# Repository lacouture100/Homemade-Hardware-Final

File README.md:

# Homemade-Hardware-Final
Repository for the development of my Homemade Hardware project.

Link to documentation: https://www.notion.so/alvarolacouture/Final-Project-Presentation-92cd7def9d2d4c558a401a928ef00175

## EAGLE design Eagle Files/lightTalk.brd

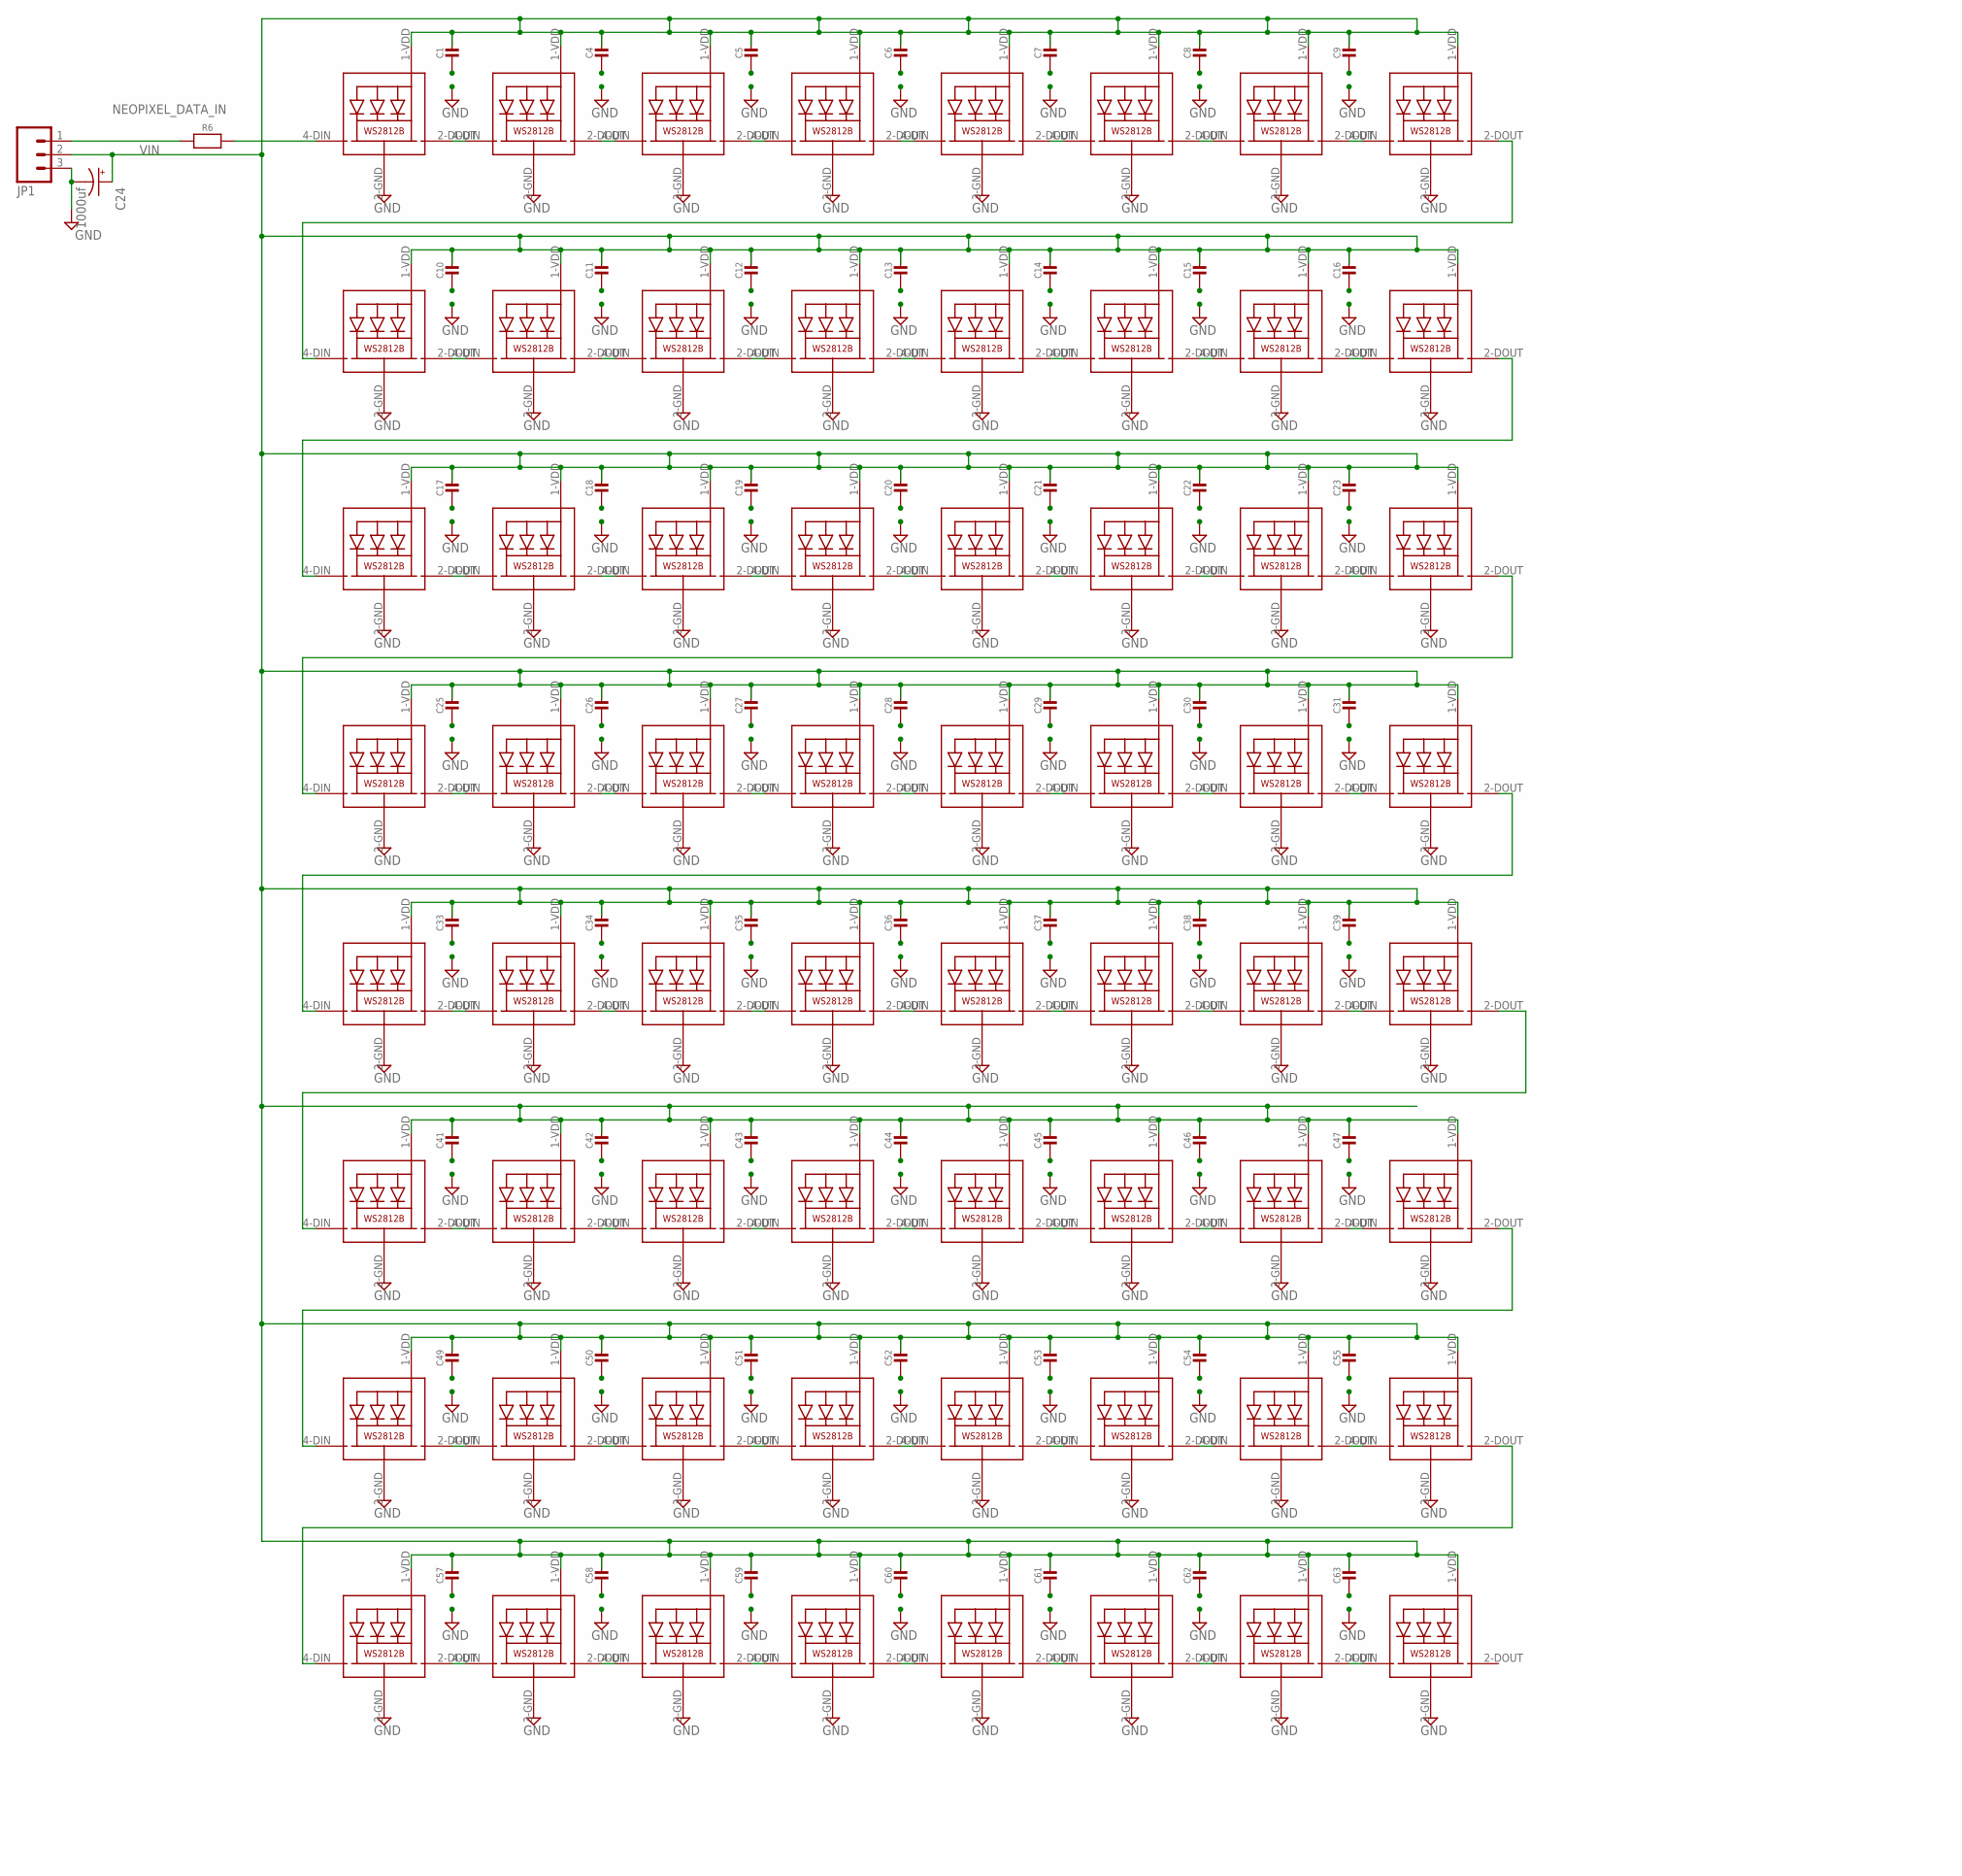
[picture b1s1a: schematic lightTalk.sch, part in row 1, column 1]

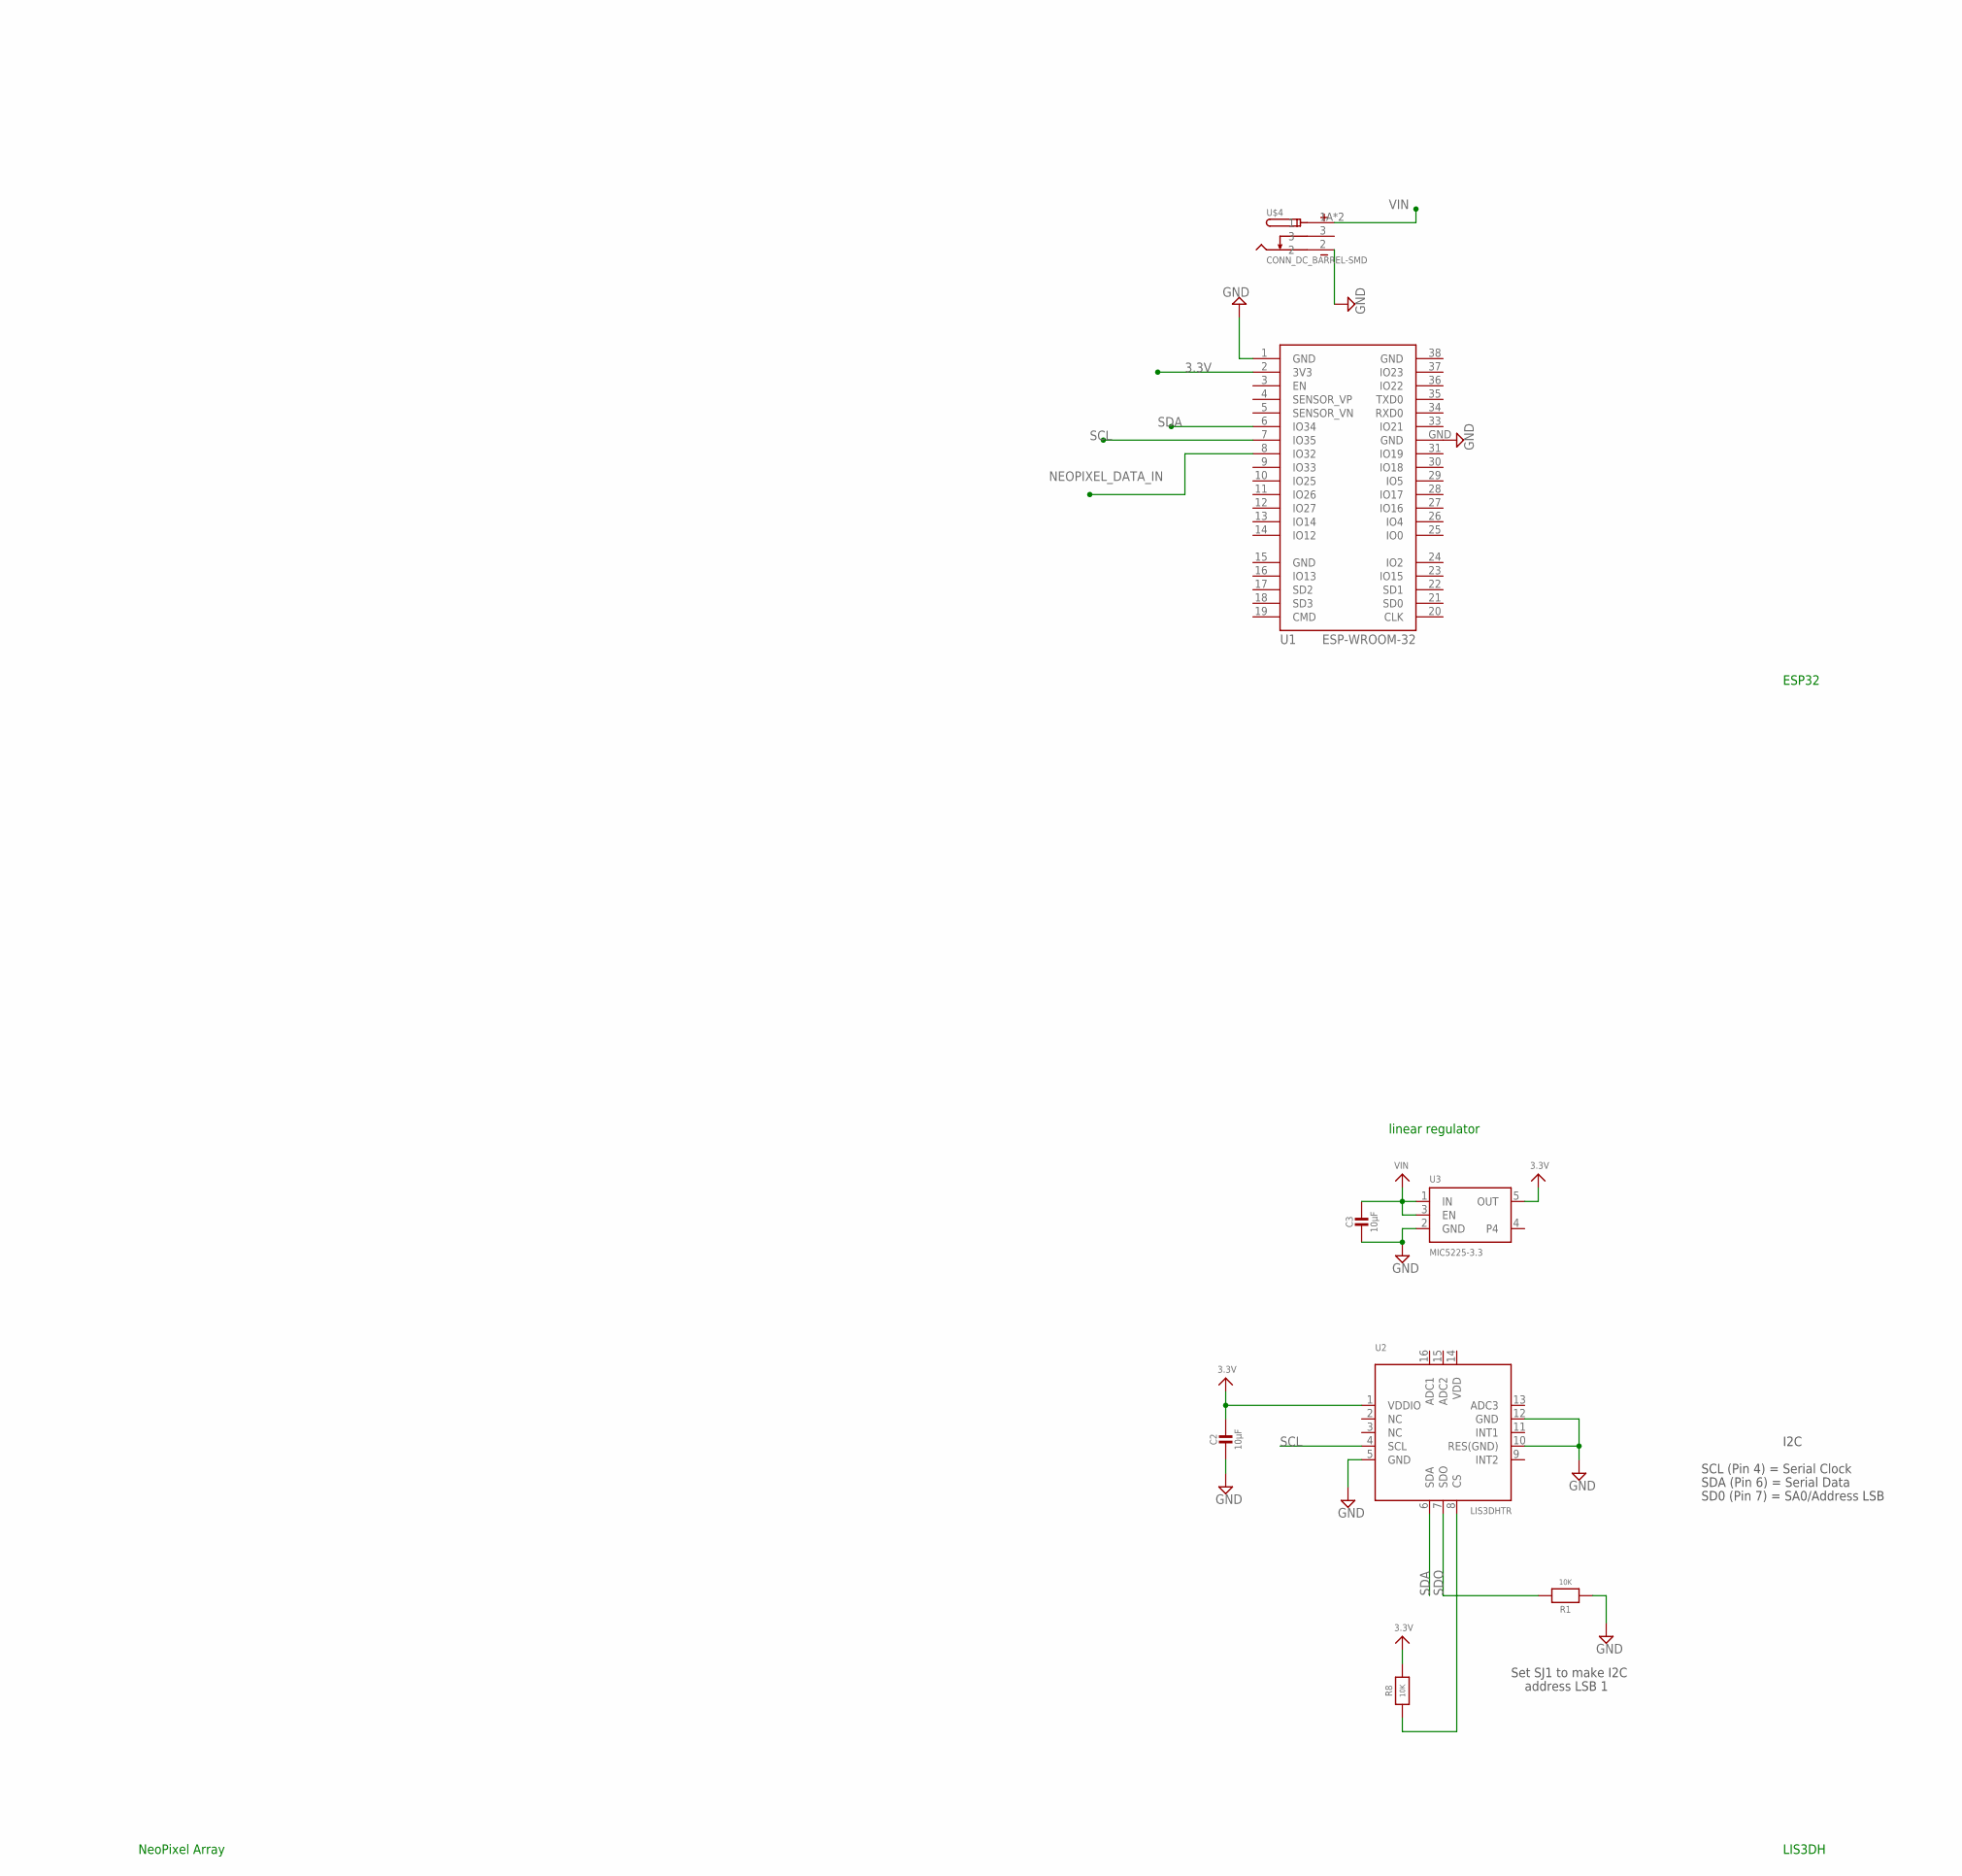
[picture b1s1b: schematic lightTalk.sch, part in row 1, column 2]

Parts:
C1, C4, C5, C6, C7, C8, C9, C10, C11, C12, C13, C14, C15, C16, C17, C18, C19, C20, C21, C22, C23, C25, C26, C27, C28, C29, C30, C31, C33, C34, C35, C36, C37, C38, C39, C41, C42, C43, C44, C45, C46, C47, C49, C50, C51, C52, C53, C54, C55, C57, C58, C59, C60, C61, C62, C63: CAP_CERAMIC0805-NOOUTLINE; 0805-NO
C2, C3: 10µF; 0805-NO
C24: 1000uf; CAP_RADIAL_CAN_10MM
JP1: M03PTH; 1X03
LED1, LED2, LED3, LED4, LED5, LED6, LED7, LED8, LED9, LED10, LED11, LED12, LED13, LED14, LED15, LED16, LED17, LED18, LED19, LED20, LED21, LED22, LED23, LED24, LED25, LED26, LED27, LED28, LED29, LED30, LED31, LED32, LED33, LED34, LED35, LED36, LED37, LED38, LED39, LED40, LED41, LED42, LED43, LED44, LED45, LED46, LED47, LED48, LED49, LED50, LED51, LED52, LED53, LED54, LED55, LED56, LED57, LED58, LED59, LED60, LED61, LED62, LED63, LED64: WS2812B5050; WS2812B
R1, R8: 10K; 0805-NO
R6: RESISTOR0805_NOOUTLINE; 0805-NO
U1: ESP-WROOM-32
U2: LIS3DHTR; LGA16_3X3MM
U3: MIC5225-3.3; SOT23-5
U$4: CONN_DC_BARREL-SMD; 694106106102

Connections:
3.3V: C2.1, R8.2, U1.2 (3V3), U2.1 (VDDIO), U3.5 (OUT)
GND: C1.2, C2.2, C3.2, C4.2, C5.2, C6.2, C7.2, C8.2, C9.2, C10.2, C11.2, C12.2, C13.2, C14.2, C15.2, C16.2, C17.2, C18.2, C19.2, C20.2, C21.2, C22.2, C23.2, C24.-, C25.2, C26.2, C27.2, C28.2, C29.2, C30.2, C31.2, C33.2, C34.2, C35.2, C36.2, C37.2, C38.2, C39.2, C41.2, C42.2, C43.2, C44.2, C45.2, C46.2, C47.2, C49.2, C50.2, C51.2, C52.2, C53.2, C54.2, C55.2, C57.2, C58.2, C59.2, C60.2, C61.2, C62.2, C63.2, JP1.3, LED1.3-GND (GND), LED2.3-GND (GND), LED3.3-GND (GND), LED4.3-GND (GND), LED5.3-GND (GND), LED6.3-GND (GND), LED7.3-GND (GND), LED8.3-GND (GND), LED9.3-GND (GND), LED10.3-GND (GND), LED11.3-GND (GND), LED12.3-GND (GND), LED13.3-GND (GND), LED14.3-GND (GND), LED15.3-GND (GND), LED16.3-GND (GND), LED17.3-GND (GND), LED18.3-GND (GND), LED19.3-GND (GND), LED20.3-GND (GND), LED21.3-GND (GND), LED22.3-GND (GND), LED23.3-GND (GND), LED24.3-GND (GND), LED25.3-GND (GND), LED26.3-GND (GND), LED27.3-GND (GND), LED28.3-GND (GND), LED29.3-GND (GND), LED30.3-GND (GND), LED31.3-GND (GND), LED32.3-GND (GND), LED33.3-GND (GND), LED34.3-GND (GND), LED35.3-GND (GND), LED36.3-GND (GND), LED37.3-GND (GND), LED38.3-GND (GND), LED39.3-GND (GND), LED40.3-GND (GND), LED41.3-GND (GND), LED42.3-GND (GND), LED43.3-GND (GND), LED44.3-GND (GND), LED45.3-GND (GND), LED46.3-GND (GND), LED47.3-GND (GND), LED48.3-GND (GND), LED49.3-GND (GND), LED50.3-GND (GND), LED51.3-GND (GND), LED52.3-GND (GND), LED53.3-GND (GND), LED54.3-GND (GND), LED55.3-GND (GND), LED56.3-GND (GND), LED57.3-GND (GND), LED58.3-GND (GND), LED59.3-GND (GND), LED60.3-GND (GND), LED61.3-GND (GND), LED62.3-GND (GND), LED63.3-GND (GND), LED64.3-GND (GND), R1.1, U1.1 (GND), U1.15 (GND), U1.38 (GND), U1.GND, U2.5 (GND), U2.10 (RES(GND)), U2.12 (GND), U3.2 (GND), U$4.2
unnamed: LED8.2-DOUT (DO), LED9.4-DIN (DI)
unnamed: R8.1, U2.8 (CS)
unnamed: LED16.2-DOUT (DO), LED17.4-DIN (DI)
unnamed: LED24.2-DOUT (DO), LED25.4-DIN (DI)
unnamed: LED40.2-DOUT (DO), LED41.4-DIN (DI)
unnamed: LED32.2-DOUT (DO), LED33.4-DIN (DI)
unnamed: LED48.2-DOUT (DO), LED49.4-DIN (DI)
unnamed: LED56.2-DOUT (DO), LED57.4-DIN (DI)
unnamed: LED1.4-DIN (DI), R6.2
unnamed: LED17.2-DOUT (DO), LED18.4-DIN (DI)
unnamed: LED25.2-DOUT (DO), LED26.4-DIN (DI)
unnamed: LED26.2-DOUT (DO), LED27.4-DIN (DI)
unnamed: LED2.2-DOUT (DO), LED3.4-DIN (DI)
unnamed: LED3.2-DOUT (DO), LED4.4-DIN (DI)
unnamed: LED4.2-DOUT (DO), LED5.4-DIN (DI)
unnamed: LED5.2-DOUT (DO), LED6.4-DIN (DI)
unnamed: LED6.2-DOUT (DO), LED7.4-DIN (DI)
unnamed: LED7.2-DOUT (DO), LED8.4-DIN (DI)
unnamed: LED10.2-DOUT (DO), LED11.4-DIN (DI)
unnamed: LED11.2-DOUT (DO), LED12.4-DIN (DI)
unnamed: LED12.2-DOUT (DO), LED13.4-DIN (DI)
unnamed: LED13.2-DOUT (DO), LED14.4-DIN (DI)
unnamed: LED14.2-DOUT (DO), LED15.4-DIN (DI)
unnamed: LED15.2-DOUT (DO), LED16.4-DIN (DI)
unnamed: LED18.2-DOUT (DO), LED19.4-DIN (DI)
unnamed: LED19.2-DOUT (DO), LED20.4-DIN (DI)
unnamed: LED20.2-DOUT (DO), LED21.4-DIN (DI)
unnamed: LED21.2-DOUT (DO), LED22.4-DIN (DI)
unnamed: LED22.2-DOUT (DO), LED23.4-DIN (DI)
unnamed: LED23.2-DOUT (DO), LED24.4-DIN (DI)
unnamed: LED27.2-DOUT (DO), LED28.4-DIN (DI)
unnamed: LED28.2-DOUT (DO), LED29.4-DIN (DI)
unnamed: LED29.2-DOUT (DO), LED30.4-DIN (DI)
unnamed: LED30.2-DOUT (DO), LED31.4-DIN (DI)
unnamed: LED31.2-DOUT (DO), LED32.4-DIN (DI)
unnamed: LED1.2-DOUT (DO), LED2.4-DIN (DI)
unnamed: LED9.2-DOUT (DO), LED10.4-DIN (DI)
unnamed: LED49.2-DOUT (DO), LED50.4-DIN (DI)
unnamed: LED57.2-DOUT (DO), LED58.4-DIN (DI)
unnamed: LED58.2-DOUT (DO), LED59.4-DIN (DI)
unnamed: LED34.2-DOUT (DO), LED35.4-DIN (DI)
unnamed: LED35.2-DOUT (DO), LED36.4-DIN (DI)
unnamed: LED36.2-DOUT (DO), LED37.4-DIN (DI)
unnamed: LED37.2-DOUT (DO), LED38.4-DIN (DI)
unnamed: LED38.2-DOUT (DO), LED39.4-DIN (DI)
unnamed: LED39.2-DOUT (DO), LED40.4-DIN (DI)
unnamed: LED42.2-DOUT (DO), LED43.4-DIN (DI)
unnamed: LED43.2-DOUT (DO), LED44.4-DIN (DI)
unnamed: LED44.2-DOUT (DO), LED45.4-DIN (DI)
unnamed: LED45.2-DOUT (DO), LED46.4-DIN (DI)
unnamed: LED46.2-DOUT (DO), LED47.4-DIN (DI)
unnamed: LED47.2-DOUT (DO), LED48.4-DIN (DI)
unnamed: LED50.2-DOUT (DO), LED51.4-DIN (DI)
unnamed: LED51.2-DOUT (DO), LED52.4-DIN (DI)
unnamed: LED52.2-DOUT (DO), LED53.4-DIN (DI)
unnamed: LED53.2-DOUT (DO), LED54.4-DIN (DI)
unnamed: LED54.2-DOUT (DO), LED55.4-DIN (DI)
unnamed: LED55.2-DOUT (DO), LED56.4-DIN (DI)
unnamed: LED59.2-DOUT (DO), LED60.4-DIN (DI)
unnamed: LED60.2-DOUT (DO), LED61.4-DIN (DI)
unnamed: LED61.2-DOUT (DO), LED62.4-DIN (DI)
unnamed: LED62.2-DOUT (DO), LED63.4-DIN (DI)
unnamed: LED63.2-DOUT (DO), LED64.4-DIN (DI)
unnamed: LED33.2-DOUT (DO), LED34.4-DIN (DI)
unnamed: LED41.2-DOUT (DO), LED42.4-DIN (DI)
NEOPIXEL_DATA_IN: JP1.1, R6.1, U1.8 (IO32)
SCL: U1.7 (IO35), U2.4 (SCL)
SDA: U1.6 (IO34), U2.6 (SDA)
SDO: R1.2, U2.7 (SDO)
VIN: C1.1, C3.1, C4.1, C5.1, C6.1, C7.1, C8.1, C9.1, C10.1, C11.1, C12.1, C13.1, C14.1, C15.1, C16.1, C17.1, C18.1, C19.1, C20.1, C21.1, C22.1, C23.1, C24.+, C25.1, C26.1, C27.1, C28.1, C29.1, C30.1, C31.1, C33.1, C34.1, C35.1, C36.1, C37.1, C38.1, C39.1, C41.1, C42.1, C43.1, C44.1, C45.1, C46.1, C47.1, C49.1, C50.1, C51.1, C52.1, C53.1, C54.1, C55.1, C57.1, C58.1, C59.1, C60.1, C61.1, C62.1, C63.1, JP1.2, LED1.1-VDD (VDD), LED2.1-VDD (VDD), LED3.1-VDD (VDD), LED4.1-VDD (VDD), LED5.1-VDD (VDD), LED6.1-VDD (VDD), LED7.1-VDD (VDD), LED8.1-VDD (VDD), LED9.1-VDD (VDD), LED10.1-VDD (VDD), LED11.1-VDD (VDD), LED12.1-VDD (VDD), LED13.1-VDD (VDD), LED14.1-VDD (VDD), LED15.1-VDD (VDD), LED16.1-VDD (VDD), LED17.1-VDD (VDD), LED18.1-VDD (VDD), LED19.1-VDD (VDD), LED20.1-VDD (VDD), LED21.1-VDD (VDD), LED22.1-VDD (VDD), LED23.1-VDD (VDD), LED24.1-VDD (VDD), LED25.1-VDD (VDD), LED26.1-VDD (VDD), LED27.1-VDD (VDD), LED28.1-VDD (VDD), LED29.1-VDD (VDD), LED30.1-VDD (VDD), LED31.1-VDD (VDD), LED32.1-VDD (VDD), LED33.1-VDD (VDD), LED34.1-VDD (VDD), LED35.1-VDD (VDD), LED36.1-VDD (VDD), LED37.1-VDD (VDD), LED38.1-VDD (VDD), LED39.1-VDD (VDD), LED40.1-VDD (VDD), LED41.1-VDD (VDD), LED42.1-VDD (VDD), LED43.1-VDD (VDD), LED44.1-VDD (VDD), LED45.1-VDD (VDD), LED46.1-VDD (VDD), LED47.1-VDD (VDD), LED48.1-VDD (VDD), LED49.1-VDD (VDD), LED50.1-VDD (VDD), LED51.1-VDD (VDD), LED52.1-VDD (VDD), LED53.1-VDD (VDD), LED54.1-VDD (VDD), LED55.1-VDD (VDD), LED56.1-VDD (VDD), LED57.1-VDD (VDD), LED58.1-VDD (VDD), LED59.1-VDD (VDD), LED60.1-VDD (VDD), LED61.1-VDD (VDD), LED62.1-VDD (VDD), LED63.1-VDD (VDD), LED64.1-VDD (VDD), U3.1 (IN), U3.3 (EN), U$4.1A (1), U$4.1B (1)

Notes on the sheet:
I2C
SCL (Pin 4) = Serial Clock
SDA (Pin 6) = Serial Data
SD0 (Pin 7) = SA0/Address LSB
Set SJ1 to make I2C
address LSB 1
linear regulator
NeoPixel Array
LIS3DH
ESP32

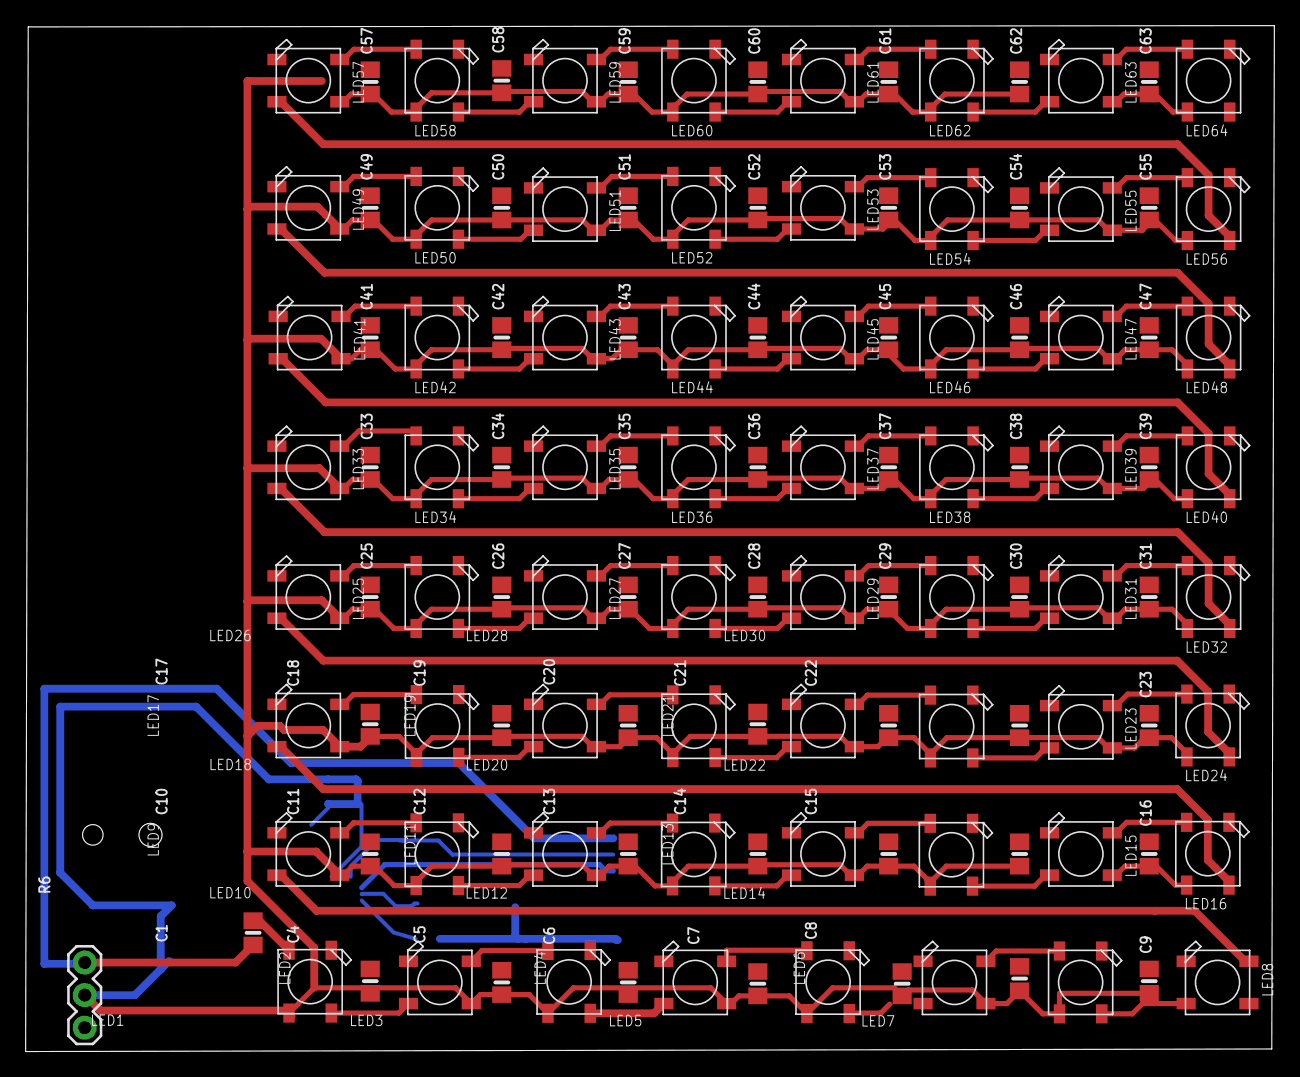
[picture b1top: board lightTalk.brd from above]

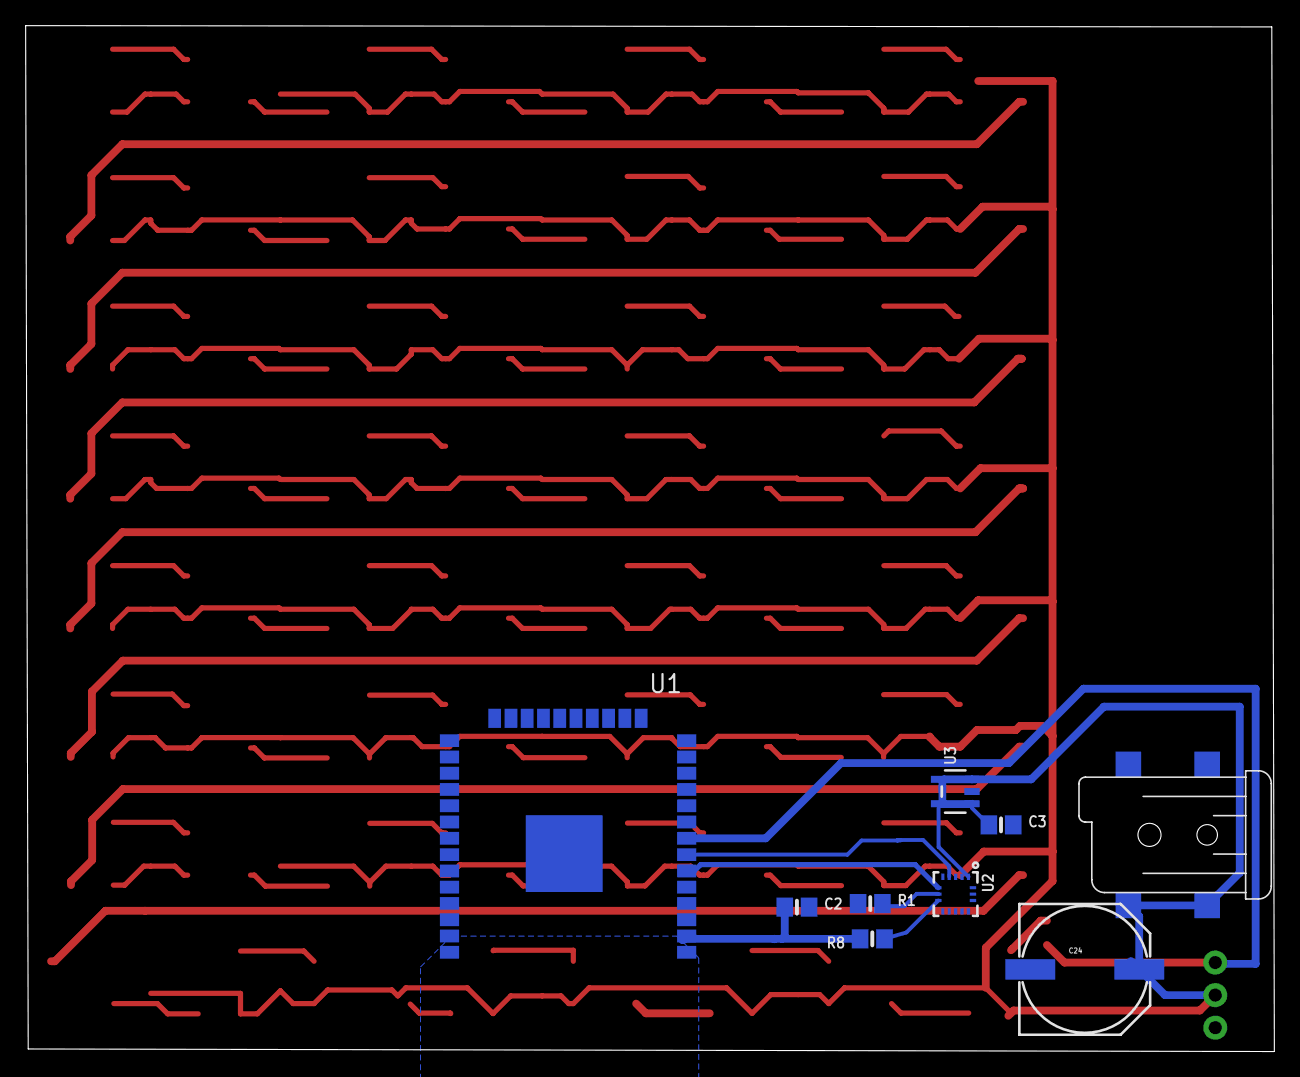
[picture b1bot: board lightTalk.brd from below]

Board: 2 copper layers, 97.4 x 80.0 mm, 131 parts (9 on the bottom side), 72 nets.

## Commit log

2020-04-03 Added arduino sketches
2020-04-24 Updated with working Websockets Server and clients
2020-05-19 Updated Notion Link
2020-12-12 Bump ini from 1.3.5 to 1.3.8 in /NodeJS/WSServer
    Bumps [ini](https://github.com/isaacs/ini) from 1.3.5 to 1.3.8.
    - [Release notes](https://github.com/isaacs/ini/releases)
    - [Commits](https://github.com/isaacs/ini/compare/v1.3.5...v1.3.8)
2021-06-11 Bump normalize-url from 4.5.0 to 4.5.1 in /NodeJS/WSServer
    Bumps [normalize-url](https://github.com/sindresorhus/normalize-url) from 4.5.0 to 4.5.1.
    - [Release notes](https://github.com/sindresorhus/normalize-url/releases)
    - [Commits](https://github.com/sindresorhus/normalize-url/commits)
    ---
    updated-dependencies:
    - dependency-name: normalize-url
2021-06-11 Bump glob-parent from 5.1.1 to 5.1.2 in /NodeJS/WSServer
    Bumps [glob-parent](https://github.com/gulpjs/glob-parent) from 5.1.1 to 5.1.2.
    - [Release notes](https://github.com/gulpjs/glob-parent/releases)
    - [Changelog](https://github.com/gulpjs/glob-parent/blob/main/CHANGELOG.md)
    - [Commits](https://github.com/gulpjs/glob-parent/compare/v5.1.1...v5.1.2)
    ---
    updated-dependencies:
2022-03-26 Bump minimist from 1.2.5 to 1.2.6 in /NodeJS/WSServer
    Bumps [minimist](https://github.com/substack/minimist) from 1.2.5 to 1.2.6.
    - [Release notes](https://github.com/substack/minimist/releases)
    - [Commits](https://github.com/substack/minimist/compare/1.2.5...1.2.6)
    ---
    updated-dependencies:
    - dependency-name: minimist
2023-02-03 Bump http-cache-semantics from 4.1.0 to 4.1.1 in /NodeJS/WSServer
    Bumps [http-cache-semantics](https://github.com/kornelski/http-cache-semantics) from 4.1.0 to 4.1.1.
    - [Release notes](https://github.com/kornelski/http-cache-semantics/releases)
    - [Commits](https://github.com/kornelski/http-cache-semantics/compare/v4.1.0...v4.1.1)
    ---
    updated-dependencies:
    - dependency-name: http-cache-semantics

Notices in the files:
parts and their libraries:
microbuilder: This work is placed in the public domain, and may be freely used for commercial and non-commercial work with the following conditions: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
esp32: Creative Commons Attribution-ShareAlike 4.0 International
